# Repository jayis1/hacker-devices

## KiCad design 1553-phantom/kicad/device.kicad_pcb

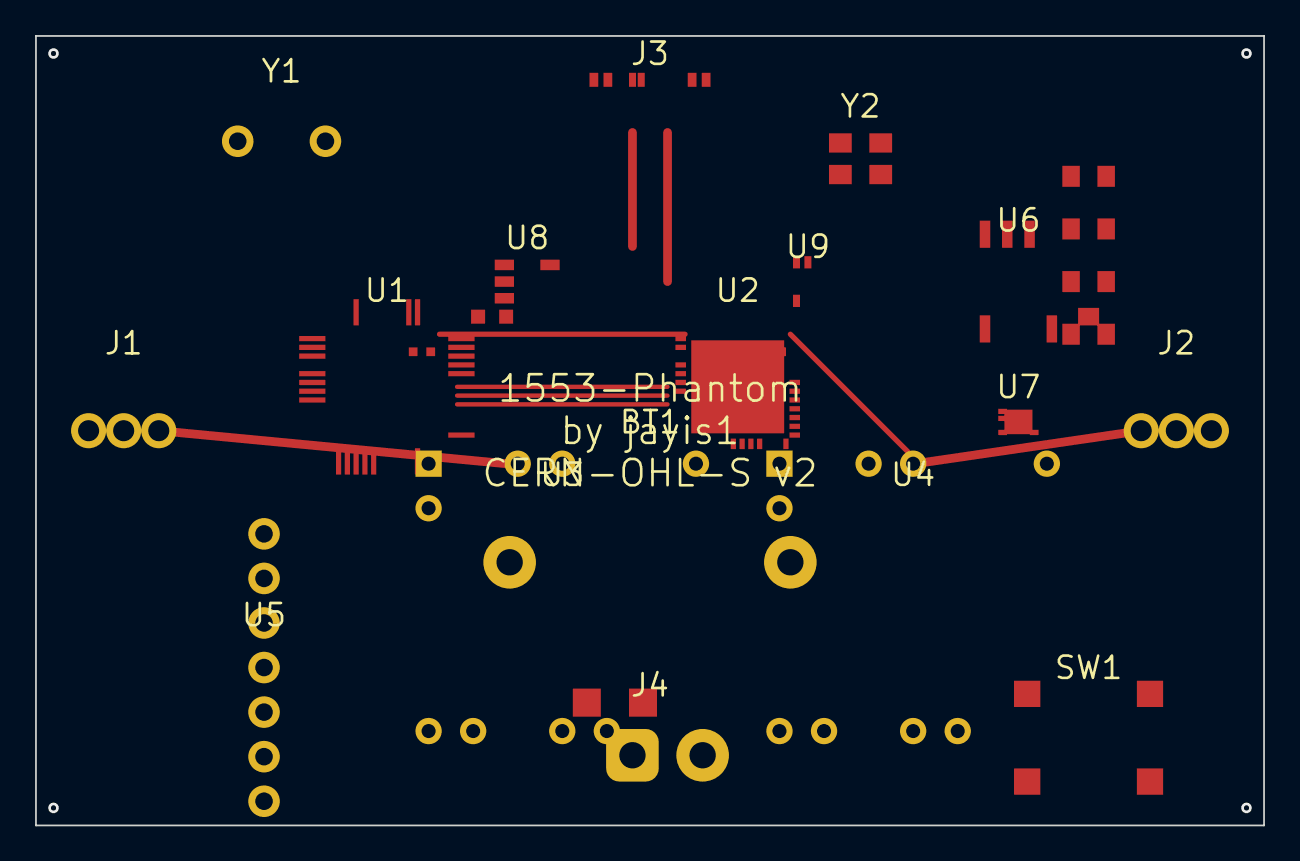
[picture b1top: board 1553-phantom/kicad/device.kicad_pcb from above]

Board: 4 copper layers, 70.0 x 45.0 mm, 25 parts (0 on the bottom side), 37 nets.

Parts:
BT1: 14500 3.7V Li-ion; BatteryHolder_Keystone_14500_1xAAA
C1, C2: 100nF; C_0402_1005Metric
C3: 10uF; C_0603_1608Metric
F1: 1A; Fuse_1206_3216Metric
J1: MIL-DTL-38999-A; Circular_MIL-DTL-38999-III-3pin
J2: MIL-DTL-38999-B; Circular_MIL-DTL-38999-III-3pin
J3: USB-C; USB_C_16pin_8x9mm
J4: 28VDC; BarrelJack_2.1x5.5mm
LED1: PWR; LED_0805_2012Metric
LED2: ACT-A; LED_0805_2012Metric
LED3: ACT-B; LED_0805_2012Metric
LED4: ARM/INJ; LED_0805_Dual_2012Metric
SW1: BTN; SW_6x6mm_4pin
U1: STM32G474CBT6; LQFP-48_7x7mm_P0.5mm
U2: iCE40-UP5K-SG48; QFN-48-1EP_7x7mm_P0.5mm_EP5.3x5.3mm
U3, U4: HI-1573PSF; PLCC-44_THT-Socket
U5: SSD1306; Connector_1x07_P2.54mm
U6: TP4056; SOIC-8_3.9x4.9mm_P1.27mm
U7: MAX17048G+T10; TDFN-8-1EP_2x2mm_P0.4mm
U8: AP2112-3.3; SOT-23-5
U9: MIC5365-1.2; SC-70-5
Y1: 16MHz; Crystal_HC49-U_Vertical
Y2: 24MHz; Crystal_SMD_3225-4Pin_3.2x2.5mm

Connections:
1553A_HI: J1.1, U3.33
1553A_LO: J1.2, U3.34
1553B_HI: J2.1, U4.33
1553B_LO: J2.2, U4.34
+1V2: C2.1, U2.1, U9.5
+3V3: C1.1, C3.1, LED1.2, LED2.2, LED3.2, LED4.A, U1.1, U2.2, U3.1, U4.1, U5.2, U7.1, U8.5, U9.1
+BATT: BT1.+, U6.5
FPGA_CLK: U2.40, Y2.1, Y2.3
FPGA_CS: U1.5, U2.30
FPGA_IRQ: U1.12, U2.43
FPGA_RST: U1.13, U2.41
FPGA_RX0_N: U2.23, U3.16
FPGA_RX0_P: U2.22, U3.15
FPGA_RX1_N: U2.27, U4.16
FPGA_RX1_P: U2.26, U4.15
FPGA_TX0_N: U2.21, U3.13
FPGA_TX0_P: U2.20, U3.12
FPGA_TX1_N: U2.25, U4.13
FPGA_TX1_P: U2.24, U4.12
GND: BT1.-, C1.2, C2.2, C3.2, J3.A1, J3.B12, J4.2, SW1.2, SW1.4, U1.17, U2.49, U3.22, U4.22, U5.1, U6.3, U7.2, U7.9, U8.2, U9.2, Y2.2, Y2.4
I2C_SCL: U1.33, U7.5
I2C_SDA: U1.34, U7.4
LED_ACTA: LED2.1, U1.24
LED_ACTB: LED3.1, U1.25
LED_ARM: LED4.1, U1.26
LED_INJ: LED4.2, U1.27
LED_PWR: LED1.1, U1.16
OLED_DC: U1.44, U5.4
OLED_RST: U1.45, U5.7
SPI_MISO: U1.7, U2.32
SPI_MOSI: U1.8, U2.33, U5.6
SPI_SCK: U1.6, U2.31, U5.5
TX_GATE: U1.28, U3.44, U4.44
USB_DM: J3.A6, U1.9
USB_DP: J3.A7, U1.10
USER_BTN: SW1.1, SW1.3, U1.11
VBUS: F1.1, F1.2, J3.A4, J3.B9, J4.1, U6.1, U6.2, U6.8, U8.1, U8.3

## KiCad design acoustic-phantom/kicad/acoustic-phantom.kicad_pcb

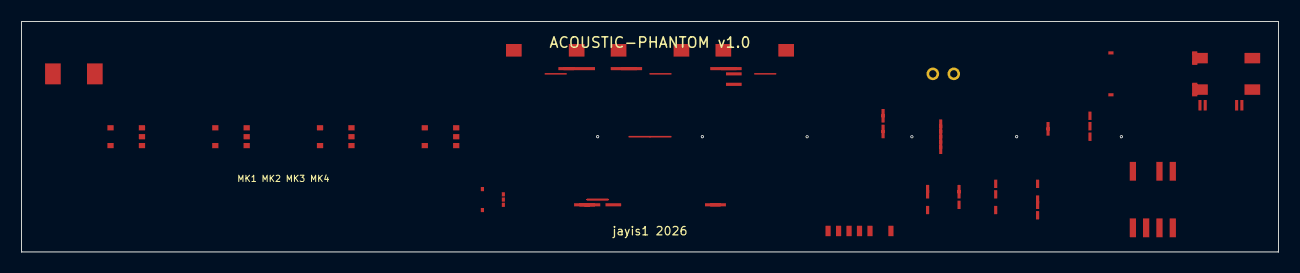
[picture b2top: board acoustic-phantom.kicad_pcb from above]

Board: 4 copper layers, 120.0 x 22.0 mm, 20 parts (0 on the bottom side), 21 nets.

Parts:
D1: WS2812B; LED_WS2812B-PLCC4
J1: USB-C-16P; USB_C_Receptacle_HRO_TYPE-C-31-M-12
J2: PZT-5H-20mm; Piezo-Jack-3.5mm
J3: MicroSD; microSD_HC_Hirose_DM3D-SF
J4: JST-PH-2; JST_PH_B2B-PH-K_1x02_P2.00mm_Vertical
MK1, MK2, MK3, MK4: SPH0641LU4H-1
SW1: POWER; SW_SPST_TL3305A
SW2: PROFILE; SW_SPST_TL3305A
SW3: ARM; SW_SPST_TL3305A
U1: STM32H743VIT6; LQFP-100_14x14mm_P0.5mm
U2: WM8904CGEFL; QFN-32-1EP_5x5mm_P0.5mm
U3: AD8233ACPZ; LFCSP-20-1EP_4x4mm_P0.5mm
U4: CYW20819; CYW20819-XXBZ
U5: W25Q128JVSIQ; SOIC-8_5.27x5.24mm_P1.27mm
U6: BQ25895RTW; QFN-24-1EP_4x4mm_P0.5mm
U7: TPS63031; VSON-10-1EP_3x3mm_P0.5mm
U9: LIS2DH12TR; LGA-12_2x2mm_P0.5mm

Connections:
+3V3: D1.1, J3.4, MK1.1, MK2.1, MK3.1, MK4.1, U1.11, U4.1, U5.8, U6.3, U6.22, U7.6, U7.8, U7.9, U9.1
AGND: J2.2, U2.2, U2.5, U3.1, U3.8
AVDD: U2.1, U3.16
BLE_RX: U1.55, U4.15
BTN_ARM: SW3.1, U1.7
BTN_PROF: SW2.1, U1.8
BTN_PWR: SW1.1, U1.14
GND: D1.3, J1.A1, J3.6, J4.2, MK1.3, MK2.3, MK3.3, MK4.3, SW1.2, SW2.2, SW3.2, U1.10, U2.31, U4.3, U4.7, U4.22, U5.4, U6.18, U7.1, U9.12
I2C1_SCL: U1.42, U2.26, U6.12, U9.4
I2C1_SDA: U1.43, U2.27, U6.11, U9.6
I2S3_CK: U1.57, U2.28
I2S3_SD: U1.54, U2.30
I2S3_WS: U1.23, U2.29
LED_DIN: D1.2, D1.4, U1.20
MIC_CLK: MK1.2, MK2.2, MK3.2, MK4.2
MIC_WS: MK1.5, MK2.5, MK3.5, MK4.5
PIEZO_IN: J2.1, U2.4, U3.7, U3.14
TAMPER: U1.9, U9.11
USB_DM: J1.A7, U1.69
VBAT: J4.1, U6.20, U7.3, U7.4
VBUS: J1.A4, U6.2

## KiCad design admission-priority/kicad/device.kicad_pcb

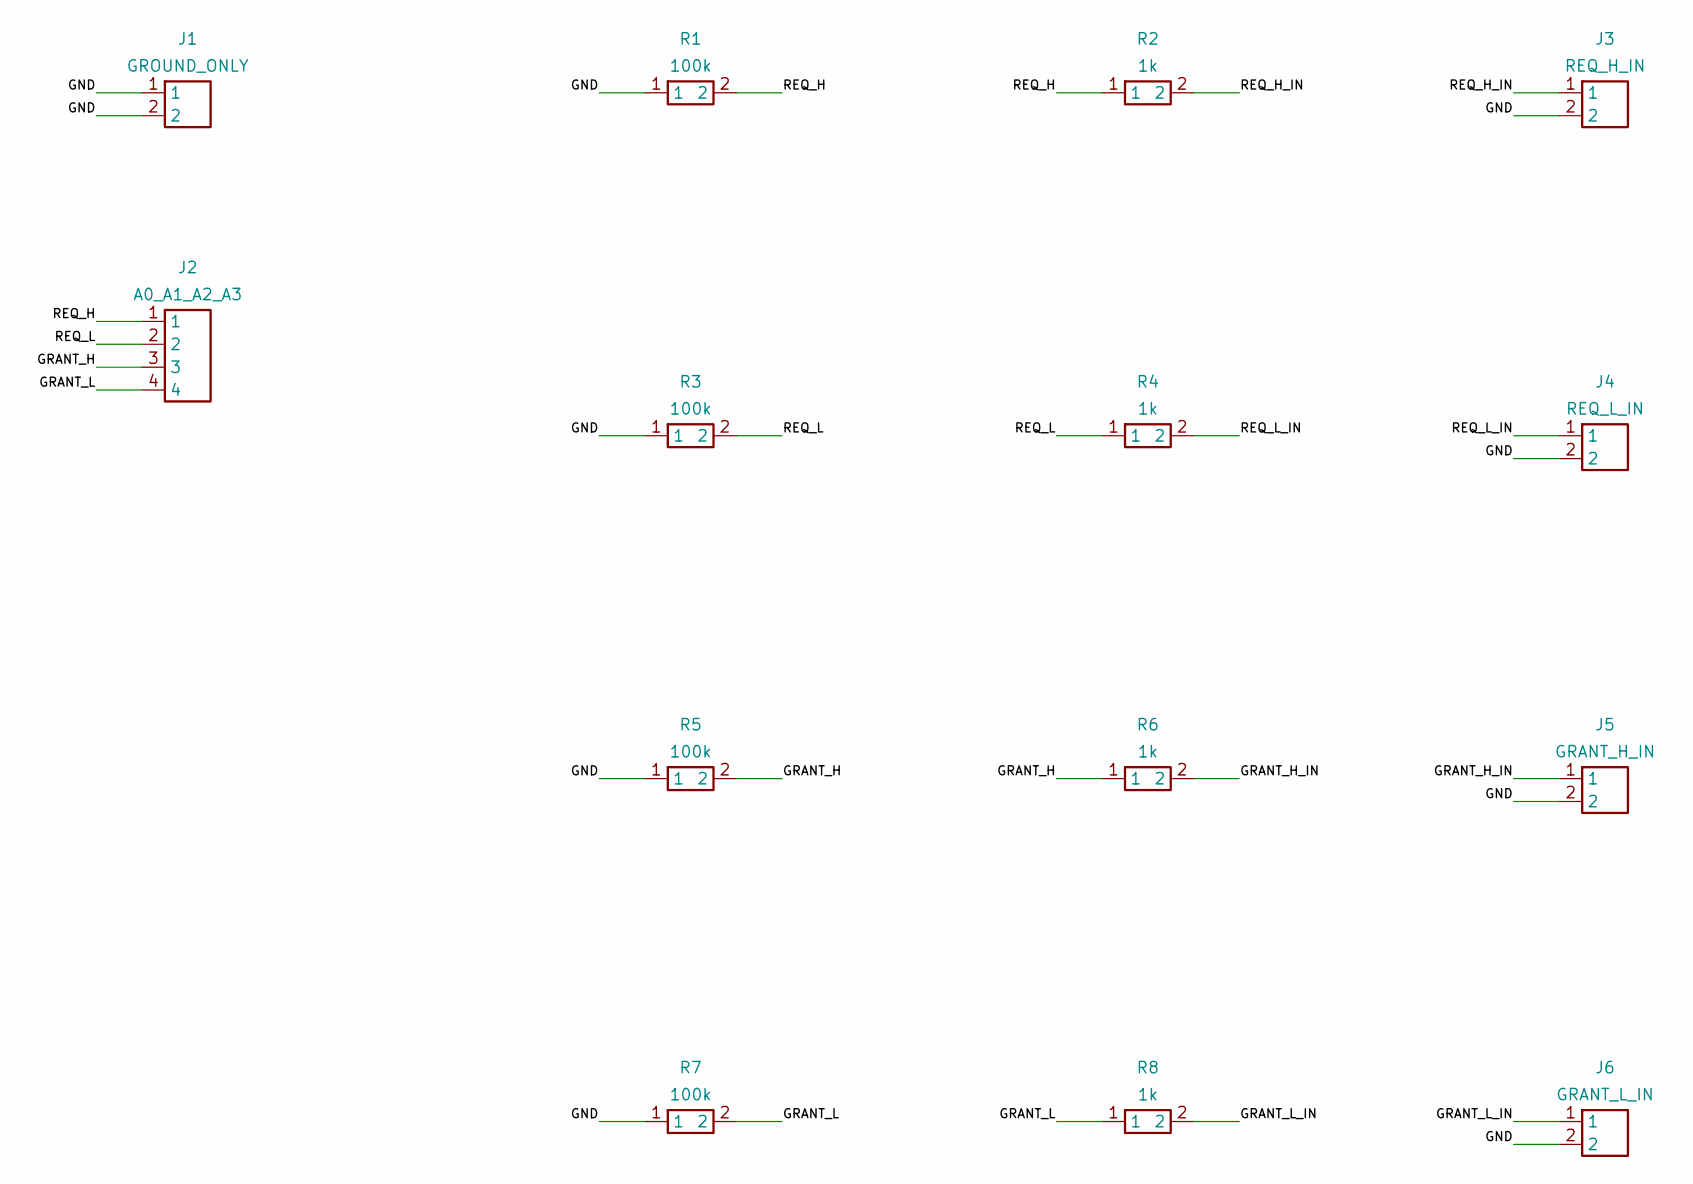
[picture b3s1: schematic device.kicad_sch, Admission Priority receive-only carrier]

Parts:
J1: GROUND_ONLY; PinHeader_1x02_P2.54mm_Vertical
J2: A0_A1_A2_A3; PinHeader_1x04_P2.54mm_Vertical
J3: REQ_H_IN; PinHeader_1x02_P2.54mm_Vertical
J4: REQ_L_IN; PinHeader_1x02_P2.54mm_Vertical
J5: GRANT_H_IN; PinHeader_1x02_P2.54mm_Vertical
J6: GRANT_L_IN; PinHeader_1x02_P2.54mm_Vertical
R1, R3, R5, R7: 100k; R_Axial_DIN0207_L6.3mm_D2.5mm_P7.62mm_Horizontal
R2, R4, R6, R8: 1k; R_Axial_DIN0207_L6.3mm_D2.5mm_P7.62mm_Horizontal

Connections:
GND: J1.1, J1.2, J3.2, J4.2, J5.2, J6.2, R1.1, R3.1, R5.1, R7.1
GRANT_H: J2.3, R5.2, R6.1
GRANT_H_IN: J5.1, R6.2
GRANT_L: J2.4, R7.2, R8.1
GRANT_L_IN: J6.1, R8.2
REQ_H: J2.1, R1.2, R2.1
REQ_H_IN: J3.1, R2.2
REQ_L: J2.2, R3.2, R4.1
REQ_L_IN: J4.1, R4.2

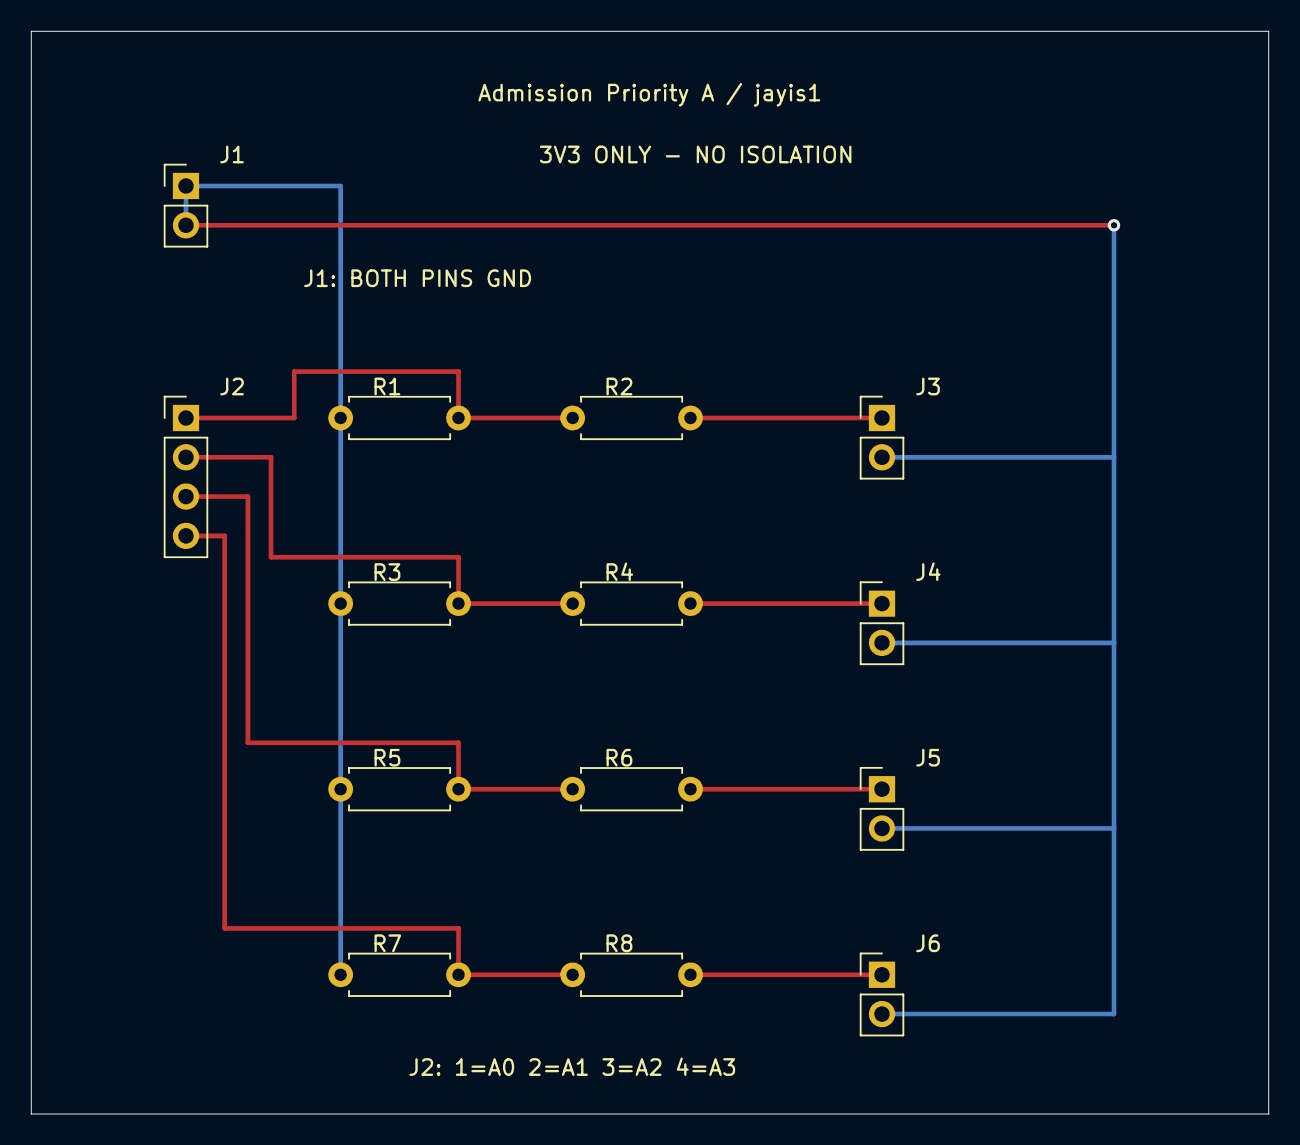
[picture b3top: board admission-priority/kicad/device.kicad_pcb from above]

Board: 2 copper layers, 80.0 x 70.0 mm, 14 parts (0 on the bottom side), 9 nets.

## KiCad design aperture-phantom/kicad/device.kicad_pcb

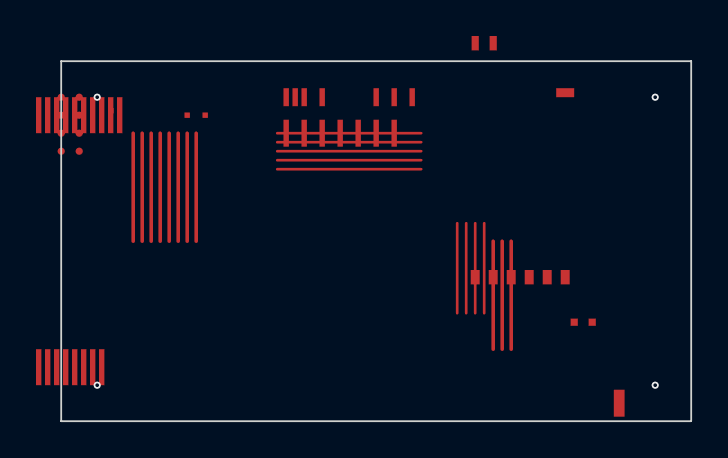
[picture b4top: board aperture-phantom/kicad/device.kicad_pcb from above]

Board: 4 copper layers, 35.0 x 20.0 mm, 12 parts (0 on the bottom side), 12 nets.

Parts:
J1: FPC22_SENSOR; Hirose_FH12-22S-0.5SH_1x22_P0.5mm_Vertical
J2: FPC22_HOST; Hirose_FH12-22S-0.5SH_1x22_P0.5mm_Vertical
J4: USB-C; USB_C_Receptacle_GCT_USB4105
J5: MicroSD; microSD_HC_Hirose_DM3D
U1: STM32H743VIT6; LQFP-100_14x14mm_P0.5mm
U2: LIFMD-25; caBGA-256_17x17mm_1.0mm
U3: IS42S16160J-7BLI; TSOP-II-54_10.16x22.22mm_P0.8mm
U4: EFR32BG22C224; QFN-32-1EP_5x5mm_P0.5mm_EP3.45x3.45mm
U5: MP2667; QFN-12-1EP_3x3mm_P0.5mm_EP1.7x1.7mm
U6: TPS62162; VQFN-8-1EP_2x2mm_P0.45mm_EP0.9x0.9mm
U7: INA219AIDC; SOT-23-8
U8: DS28E07-100; SOT-223-3_TabPin2

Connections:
CSI_CLK_N: J1.3, J2.3, U2.D1
CSI_CLK_P: J1.4, J2.4, U2.D2
CSI_D0_N: J1.5, J2.5, U2.B1
CSI_D0_P: J1.6, J2.6, U2.B2
CSI_D1_N: J1.7, J2.7, U2.C1
CSI_D1_P: J1.8, J2.8, U2.C2
GND: J1.2, J2.2, J4.A1, J4.B12, J5.3, U1.1, U2.A1, U3.2, U4.2
USB_DM: J4.A10, J4.B10
USB_DP: J4.A11, J4.B11
VANA_SENS: J1.1, J2.1, U7.1
VBAT: U5.1, U6.1
VCC_3V3: J4.A5, J5.4, U1.2, U2.A2, U3.1, U4.1, U6.2

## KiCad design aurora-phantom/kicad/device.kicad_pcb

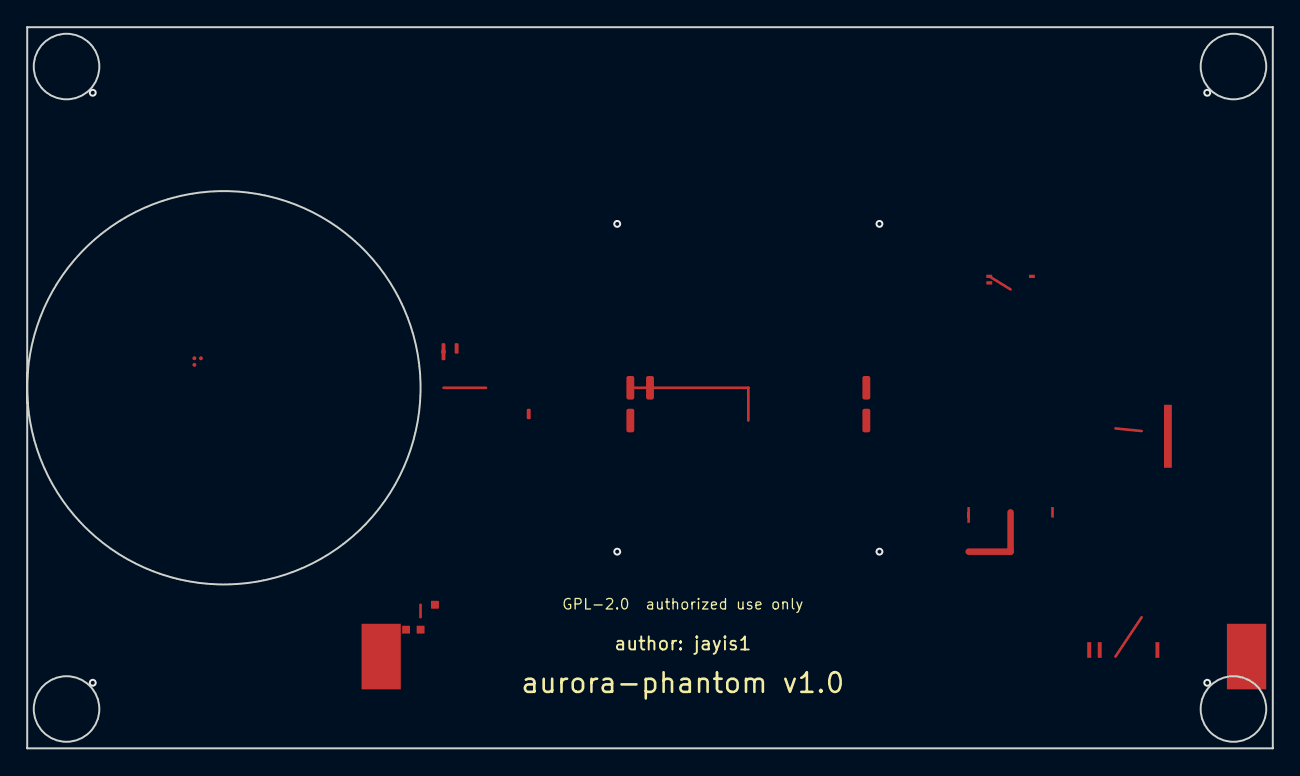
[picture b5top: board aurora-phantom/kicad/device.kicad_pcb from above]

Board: 4 copper layers, 95.0 x 55.0 mm, 9 parts (0 on the bottom side), 4 nets.

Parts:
BT1: 18650_3.7V; BatteryHolder_Keystone_1042_1x18650
J1: microSD_4-bit; microSD_HC_Hirose_DM3D-SF
J2: USB-C-16P; USB_C_Receptacle_GCT_USB4135
U1: ESP32-S3-WROOM-1; ESP32-WROOM-32
U2: iCE40UP5K-SG48; QFN-48-1EP_7x7mm_P0.5mm
U3: SPAD-16x16-TDC; SPAD_BGA_256
U4: Si5351C-B-GT; MSOP-10_3x3mm_P0.5mm
U5: nPM1300; QFN-56-1EP_7x7mm_P0.4mm
U6: MCP4725; SOT-23-6

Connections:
3V3: J1.2, U1.2, U4.2, U5.3, U6.2
CLK_40M: U2.35, U4.7
GND: BT1.2, J1.1, J2.A1, U1.1, U2.1, U3.A1, U4.1, U5.1, U6.1
VBAT: BT1.1, U5.2

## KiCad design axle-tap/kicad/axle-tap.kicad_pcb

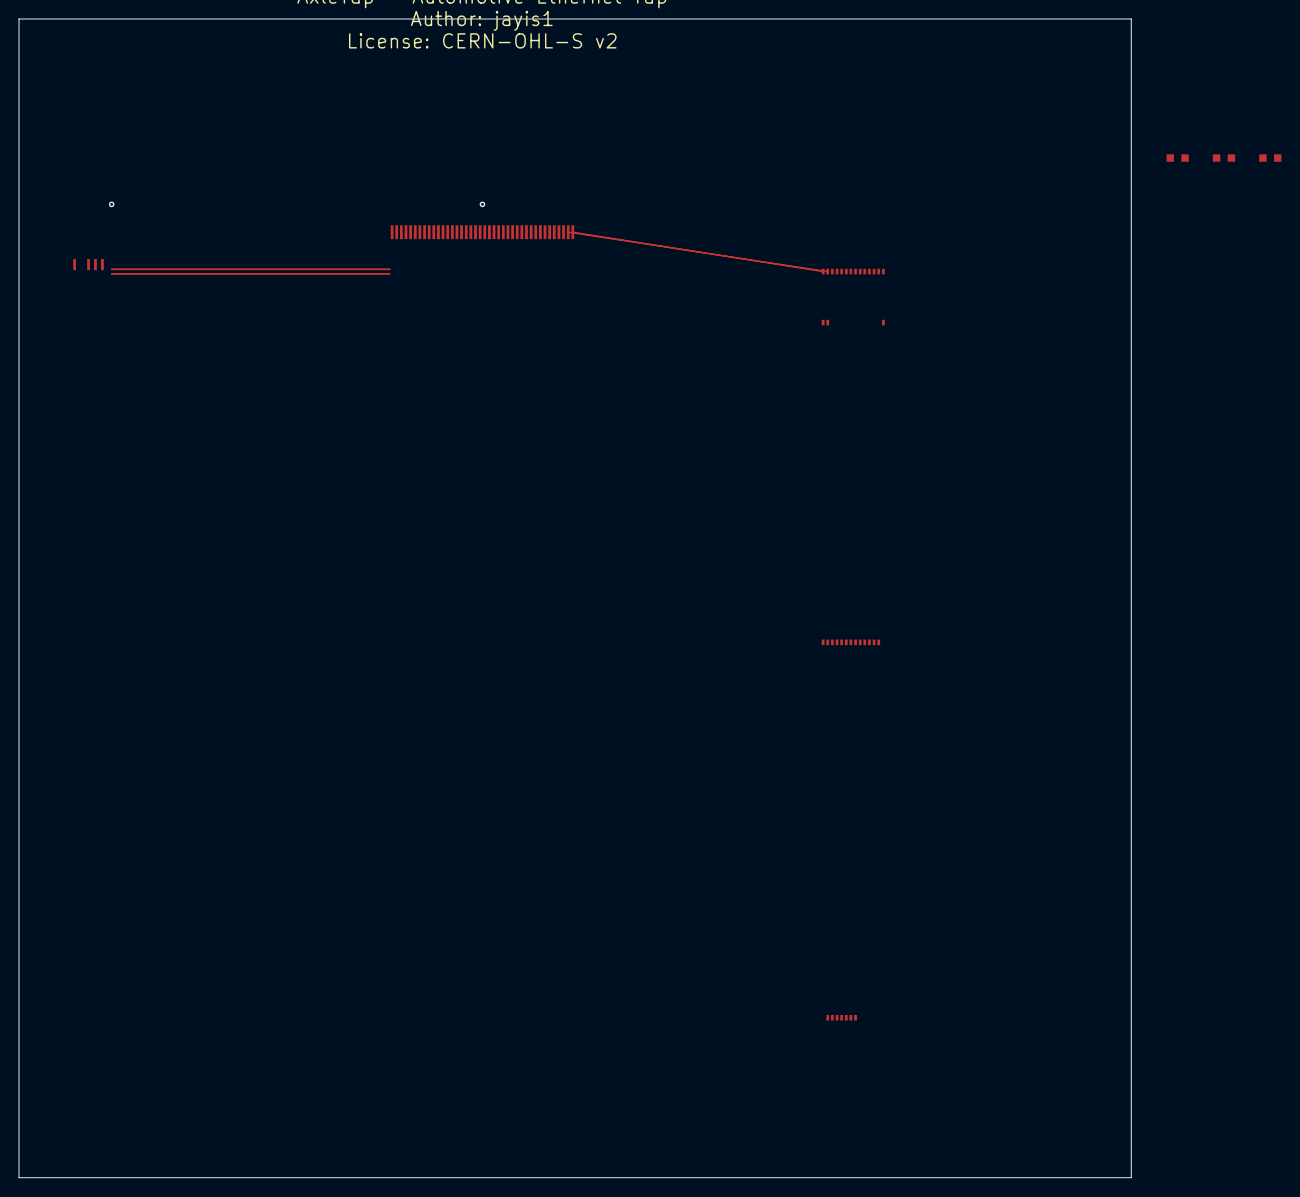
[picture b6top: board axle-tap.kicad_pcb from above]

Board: 4 copper layers, 120.0 x 125.0 mm, 8 parts (0 on the bottom side), 27 nets.

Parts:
D1: LED_LINKA; LED_0603_1608Metric
D2: LED_LINKB; LED_0603_1608Metric
D3: LED_ARM; LED_0603_1608Metric
J1: USB_C_Receptacle; USB_C_Receptacle_USB2.0
U1: STM32H723ZGT6; LQFP-144_20x20mm_P0.5mm
U2, U3: 88Q2112; QFN-48-1EP_7x7mm_P0.5mm_EP5.6x5.6mm
U4: nRF52820; QFN-40-1EP_6x6mm_P0.5mm_EP4.6x4.6mm

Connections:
BLE_CS: U1.26, U4.4
BLE_IRQ: U1.27, U4.5
GND: D1.2, D2.2, D3.2, J1.A1, U4.7
LED_ARM: D3.1, U1.30
LED_LINKA: D1.1, U1.28
LED_LINKB: D2.1, U1.29
MDC: U1.12, U2.14, U3.10
MDIO: U1.7, U2.13, U3.9
PHYA_RESET: U1.8, U2.15
PHYB_RESET: U1.9, U3.11
RGMII_RXD0_A: U1.15, U2.9
RGMII_RXD1_A: U1.16, U2.10
RGMII_RXD2_A: U1.5, U2.11
RGMII_RXD3_A: U1.6, U2.12
RGMII_RX_CLK_A: U1.3, U2.7
RGMII_RX_DV_A: U1.10, U2.8
RGMII_TXD0_A: U1.4, U2.3
RGMII_TXD1_A: U1.11, U2.4
RGMII_TXD2_A: U1.13, U2.5
RGMII_TXD3_A: U1.14, U2.6
RGMII_TX_CLK_A: U1.1, U2.1
RGMII_TX_EN_A: U1.2, U2.2
SPI6_MISO: U1.25, U4.3
SPI6_MOSI: U1.24, U4.2
SPI6_SCK: U1.23, U4.1
USB_DM: J1.B12, U1.39
USB_DP: J1.B9, U1.40

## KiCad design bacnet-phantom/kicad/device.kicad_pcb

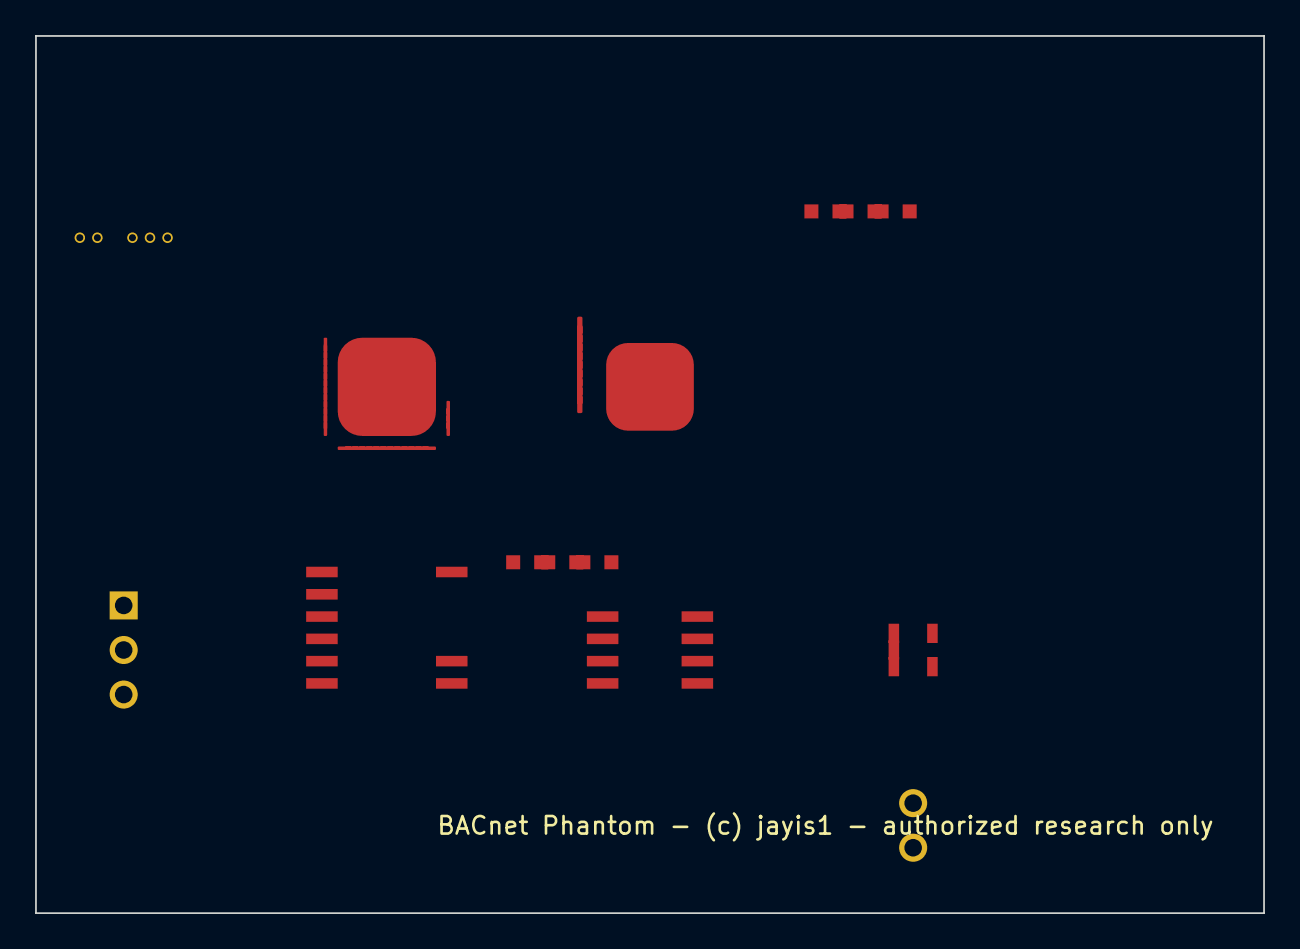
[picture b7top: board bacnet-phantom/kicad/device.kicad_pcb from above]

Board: 2 copper layers, 70.0 x 50.0 mm, 14 parts (0 on the bottom side), 26 nets, no tracks yet.

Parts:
D1: RED; LED_0603
D2: GRN; LED_0603
D3: BLU; LED_0603
J1: USB_C_2.0; USB_C_Receptacle_USB2.0
J2: RS485_HDR; PinHeader_1x03
J3: WP_BYPASS; PinHeader_1x02
R1, R2: 10k; R_0603
R3: 100k; R_0603
U1: ESP32-S3-WROOM-1-N16R8; QFN-56-1EP_7x7mm_P0.4mm_EP5.6x5.6mm
U2: W5500; LQFP-48_7x7mm_P0.5mm
U3: ISO1500; SOIC-16_3.9x9.9mm_P1.27mm
U4: MAX3491ESA; SOIC-8_3.9x4.9mm_P1.27mm
U5: TP4056; SOT-23-5

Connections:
+3V3: D1.2, D2.2, D3.2, J3.1, R1.1, U1.1, U1.39, U2.1, U3.1, U3.2, U3.8, U4.1
+5V: U1.25, U1.26, U2.10
BATT_DIV: R3.2, U1.22
CHRG: U1.20, U5.4
GND: J1.A1, J2.3, R2.1, U1.2, U1.40, U1.EP, U2.2, U2.EP, U3.9, U3.16, U4.6, U5.2
LED_B: D3.1, U1.19
LED_G: D2.1, U1.18
LED_R: D1.1, U1.17
MSTP_DE: U1.13, U3.4, U4.2
MSTP_RE_N: U1.14, U3.5, U4.3
MSTP_RX: U1.12, U3.6, U4.5
MSTP_TX: U1.11, U3.3, U4.4
RS485_A: J2.1, R1.2, U4.7
RS485_B: J2.2, R2.2, U4.8
SPI_MISO: U1.4, U2.4
SPI_MOSI: U1.3, U2.3
SPI_SCLK: U1.5, U2.5
STDBY: U1.21, U5.5
USB_DM: J1.A7, U1.24
USB_DP: J1.A6, U1.23
VBAT: R3.1, U5.3
VBUS: J1.A4, J1.B12, U1.41, U1.42, U2.9, U5.1
W5500_CS: U1.6, U2.6
W5500_INT: U1.8, U2.8
W5500_RST: U1.7, U2.7
WP_JUMPER: J3.2, U1.15

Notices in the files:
1553-phantom/kicad/device.kicad_pcb:
CERN-OHL-S v2
1553-phantom/kicad/device.kicad_sch:
License: CERN-OHL-S v2
aperture-phantom/kicad/device.kicad_pcb:
License: GPL-2.0
aurora-phantom/kicad/device.kicad_pcb:
GPL-2.0  authorized use only
bacnet-phantom/kicad/device.kicad_sch:
License: CERN-OHL-W v2 (hardware)
